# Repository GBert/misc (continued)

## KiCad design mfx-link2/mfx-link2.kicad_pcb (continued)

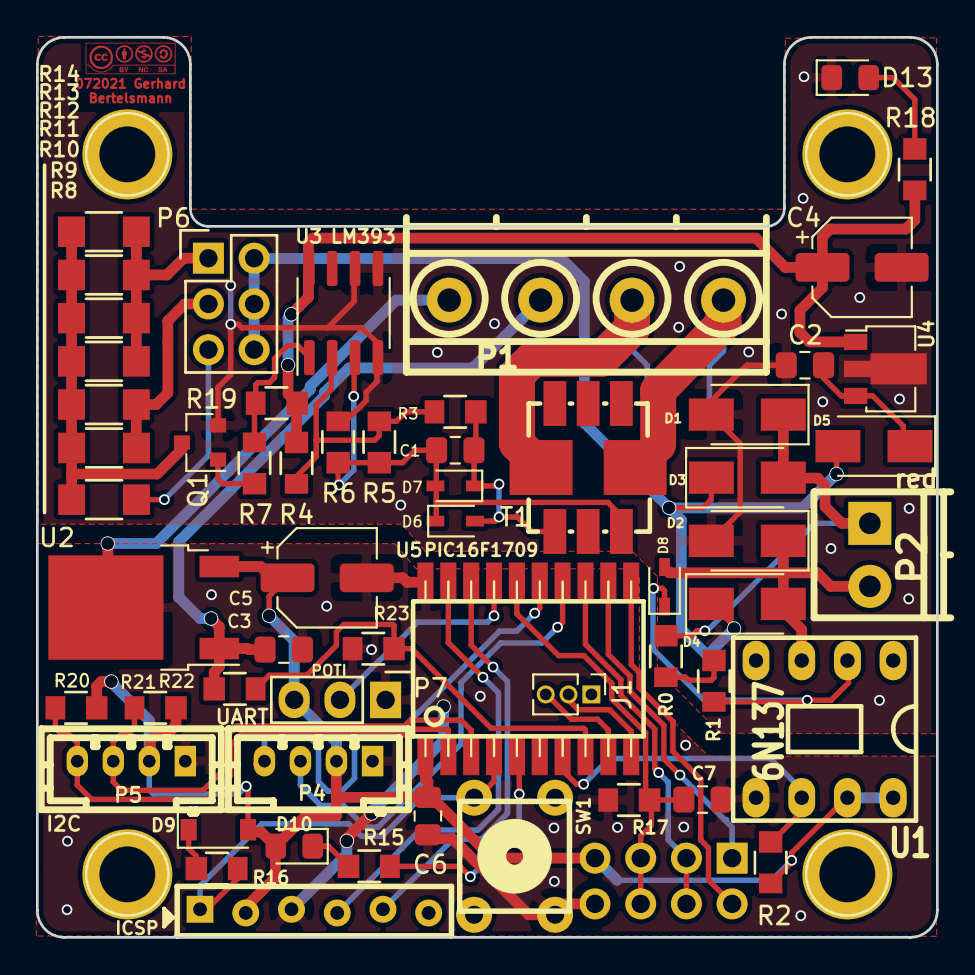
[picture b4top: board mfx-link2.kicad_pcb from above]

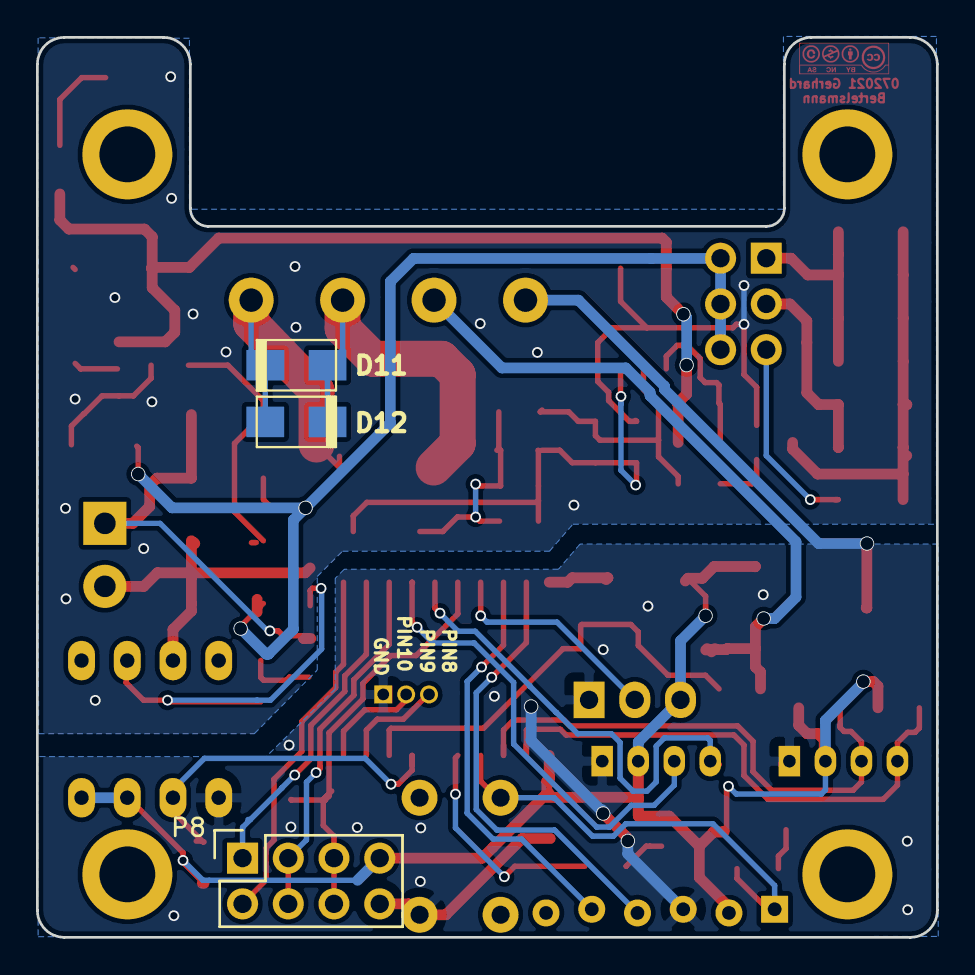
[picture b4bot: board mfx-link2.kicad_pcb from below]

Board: 2 copper layers, 50.0 x 50.0 mm, 61 parts (3 on the bottom side), 42 nets.

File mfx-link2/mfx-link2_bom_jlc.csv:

"Comment","Designator","Footprint","LCSC Part #"
"100nF","C6,C1,C3,C2","C_0805_2012Metric_Pad1.18x1.45mm_HandSolder","C49678"
"1nF","C7","C_0805_2012Metric_Pad1.18x1.45mm_HandSolder","C46653"
"US1M","D4,D3,D2,D5,D12,D11,D1","D_SMA","C412437"
"1N4148","D6,D7,D8","D_SOD-323F","C2128"
"B5819W","D9","D_SOD-123","C8598"
"LEDR","D10","LED_0805","C84256"
"LED","D13","LED_0805","C34499"
"MMBT5551","Q1","SOT-23","C2145"
"820","R1,R0","R_0805_HandSolderingII","C17837"
"390","R2","R_0805_HandSolderingII","C17655"
"22","R3","R_0805_HandSolderingII","C17561"
"82","R5","R_0805_HandSolderingII","C17841"
"1k","R7","R_0805_HandSolderingII","C17513"
"1K","R9,R8","R_1206_HandSolderingII","C4410"
"1k","R11,R12,R13,R14,R10","R_1206_HandSolderingII","C4410"
"1k5","R15","R_0805_HandSolderingII","C4310"
"4k7","R16,R6,R4,R19","R_0805_HandSolderingII","C17673"
"10k","R17,R23","R_0805_HandSolderingII","C17414"
"560","R18","R_0805_HandSolderingII","C28636"
"3k3","R20,R21","R_0805_HandSolderingII","C26010"
"39k","R22","R_0805_HandSolderingII","C25826"
"7805","U2","TO-252-2","C58069"
"LM393","U3","SOIC-8_3.9x4.9mm_P1.27mm","C7955"
"78L05","U4","SOT-89-3","C71136"

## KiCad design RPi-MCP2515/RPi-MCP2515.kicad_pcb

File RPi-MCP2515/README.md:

RPI-I2C/CAN Adapter mit galv. Trennung
======================================

Hinweis
-------
In der Platinen-Version 1.0 hatte sich ein Fehler eingeschlichen so das der Längsregler MC7805 spiegelverkehrt eingebaut werden musste. Das ist mit der Version >= 1.1 behoben, d.h. das der Längsregler wie auf dem Bestückungsdruck ersichtlich eingebaut werden muss.

[Reichelt Liste (ohne P82B715P)](https://www.reichelt.de/my/1344615) Variante mit galvanischer Trennung und externer Spannungsversorgung

Bauteilliste
------------
(galv. Trennung mit ISO1050)
```
C1,C2	22pF
C3-C9	100nF
D1	LED 2mA
P1	Buchsenleiste 2x20
P6	Steckerleiste 1x2
P9	Groove Buchse gewinkelt
P17	Steckerleiste 1x2
R1-R3	4k7 Ohm
R5	1k5 Ohm
R13	120 Ohm
R14,R15	3k3 Ohm
R24,R25	3k3 Ohm
U1	MCP2515
U3	(P82B715 optional)
U6	ISO1050
U7	LM7805
Y1	16MHz Quarz
```

Aufbau
------
Die CAN-Anbindung erfolgt bei der Nutzung des ISO1050 über P7 mit VCOM (7-24V), GND, CANL und CANH.

Wird ein galv. getrennter DCDC Konverter verwendet so sind nur GND, CANL und CANH zu verbinden. 

Sollte ein MCP2562 eingesetzt werden erfolgt die Anbindung über P3.

Nutzung MS2 Kabel E146781
-------------------------

|Farbe	  |Funktion|
|---------|--------|
|schwarz  |	GND|	
|braun	  |    CANL|	
|orange   |    CANH|	
|rot      | 18V Vcc|

Nutzung
-------

Mit dem I2C Interface kann man die preiswerten [PI02](http://wiki.rocrail.net/doku.php?id=gca_pi02-de) nutzen.
pio-i2c-udp setzt Events in das M\*rklin Format um und stellt sich als S88 dar.

CAN Nutzung vorbereiten
```
sudo apt-get update
sudo apt-get upgrade
sudo apt-get install can-utils
```
/boot/config.txt editieren
```
; uncomment
dtparam=spi=on
; add
dtoverlay=mcp2515-can0,oscillator=16000000,interrupt=25
```
reboot
```
sudo shutdown -r now
```
CAN Interface konfigurieren
```
sudo ip link set can0 up type can bitrate 250000 restart-ms 100
```
bzw: die Datei /etc/network/interfaces.d/can0 wie folgt anlegen:
```
auto can0
iface can0 inet manual
        pre-up /sbin/ip link set $IFACE type can bitrate 250000 restart-ms 100
        up /sbin/ifconfig $IFACE up
        down /sbin/ifconfig $IFACE down
```
can2lan nutzen
```
sudo apt-get install lighttpd
# zumindest geraet.vrs unter /var/www/html/config/ anlegen:
sudo mkdir -p /var/www/html/config/
sudo cat << EOF > /var/www/html/config/geraet.vrs
[geraet]
version
 .minor=1
geraet
 .sernum=1
 .hardvers=RPi,3
EOF

```
can2lan herunter laden und starten
```
cd
sudo apt-get install git libpcap-dev
git clone https://github.com/GBert/railroad.git
cd railroad/can2udp/src
make
sudo cp can2lan /usr/sbin/
sudo cp can-monitor /usr/bin/
sudo cp ../files/maerklin/config/gleisbild.cs2 /var/www/html/gleisbild.cs2

# Debian  Init Skript installieren und testen
sudo cp ../debian/can2lan.init /etc/init.d
sudo /etc/init.d/can2lan.init start
sudo /etc/init.d/can2lan.init status
sudo /etc/init.d/can2lan.init stop

sudo update-rc.d can2lan.init defaults

# oder manuell im Vordergrund start
can2lan -mvf -c /var/www/html
```

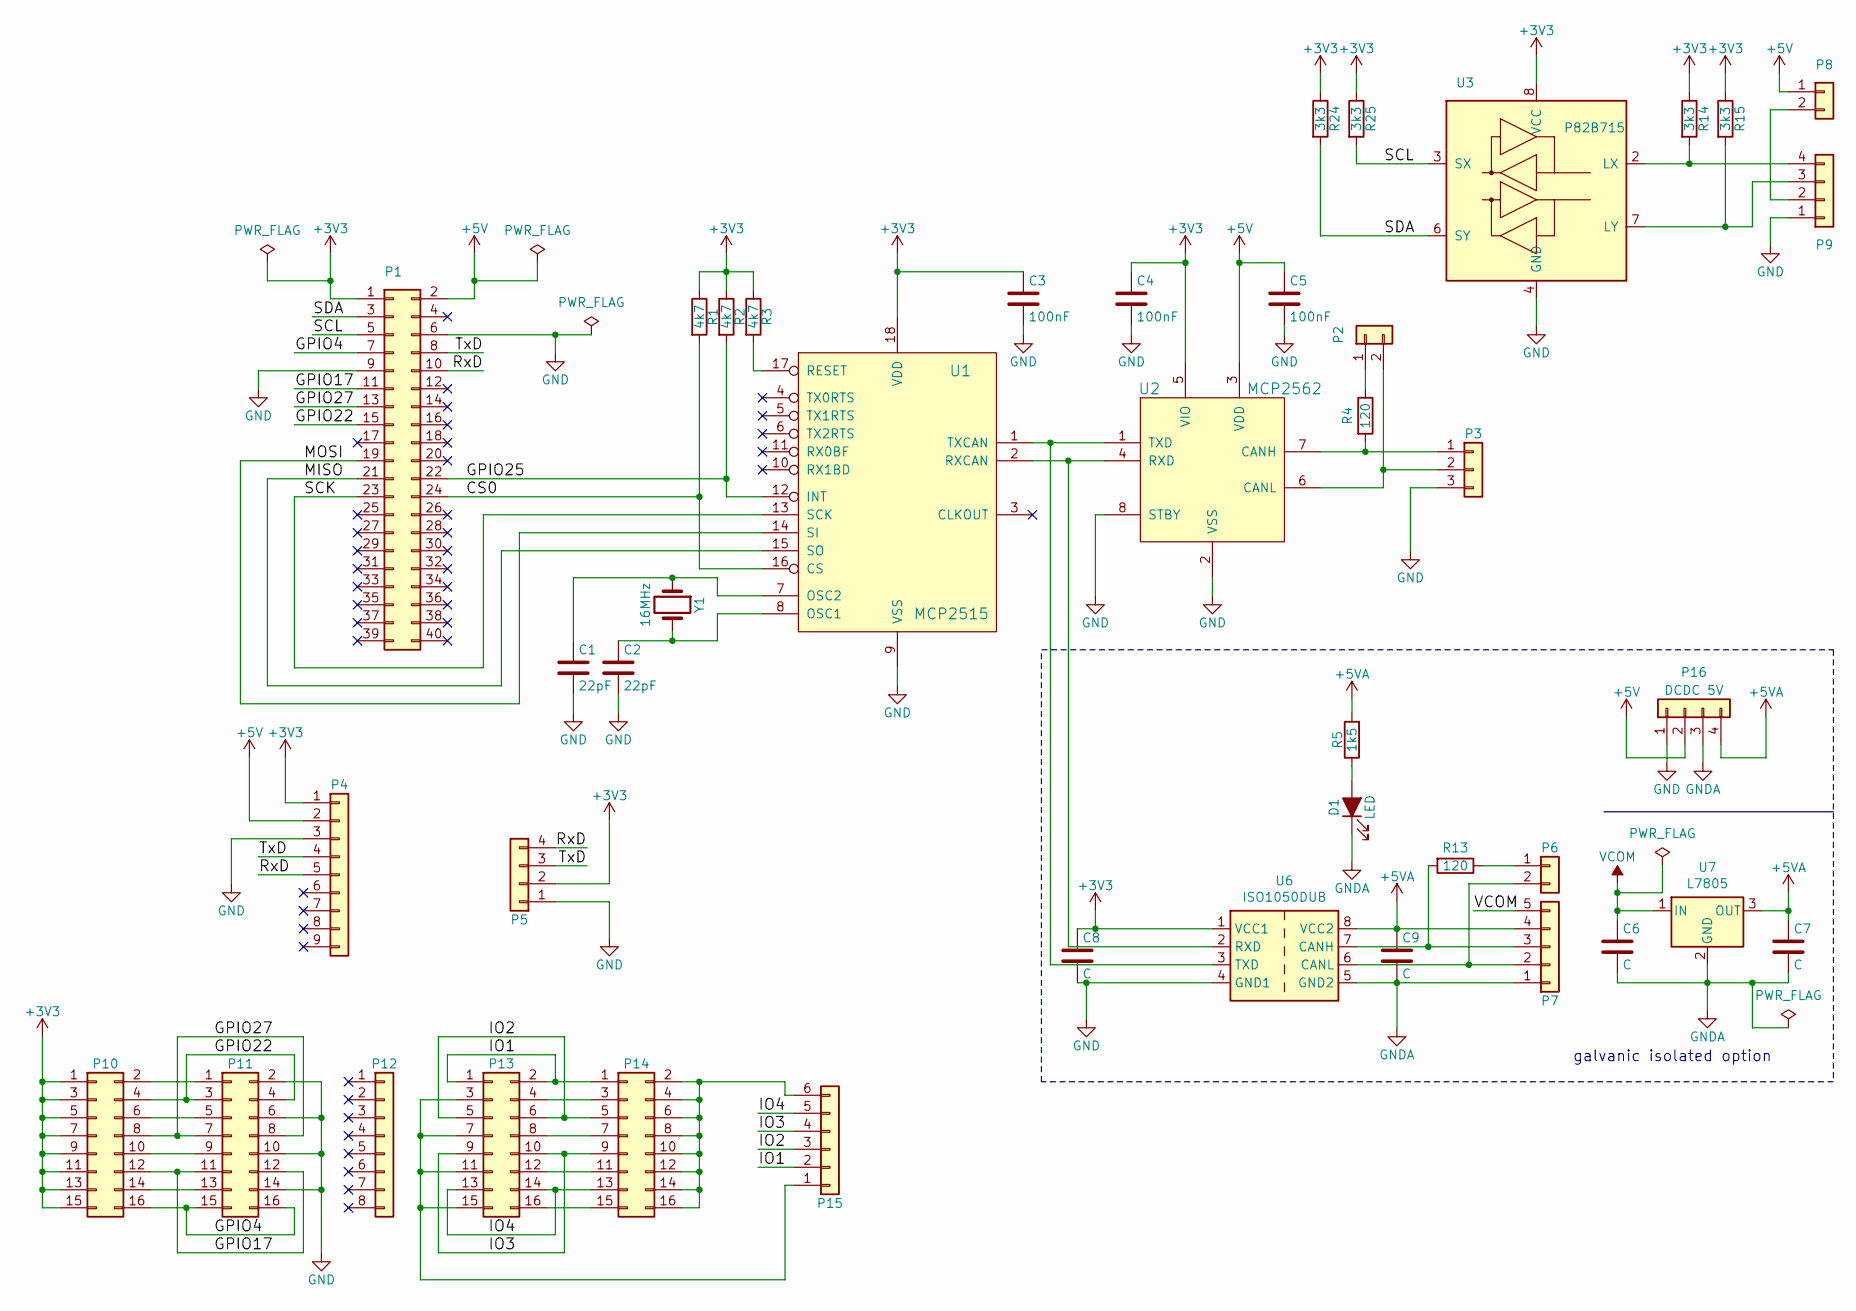
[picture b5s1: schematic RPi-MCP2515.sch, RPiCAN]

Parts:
C1, C2: 22pF; C_Disc_D3_P2.5
C3, C4, C5: 100nF; C_Disc_D3_P2.5
C6, C7, C8, C9: C; C_Disc_D3_P2.5
D1: LED; LED-5MM
P1: CONN_02X20; Socket_Strip_Straight_2x20
P2, P6, P8: CONN_01X02; Pin_Header_Straight_1x02
P3: CONN_01X03; Pin_Header_Angled_1x03
P4: CONN_01X09; Pin_Header_Straight_1x09
P5, P9: CONN_01X04; s4b-ph-kl
P7: CONN_01X05; pt_1,5-5-3,5-h
P10, P11, P13, P14: CONN_02X08; Socket_Strip_Straight_2x08
P12: CONN_01X08; Socket_Strip_Straight_1x08
P15: CONN_01X06; Socket_Strip_Straight_1x06
P16: DCDC 5V; dcdc_sil4
R1, R2, R3: 4k7; RC03
R4, R13: 120; RC03
R5: 1k5; RC03
R14, R15, R24, R25: 3k3; RC03
U1: MCP2515; dil_18-300_socket
U2: MCP2562; dil_8-300_socket
U3: P82B715; dil_8-300_socket
U6: ISO1050DUB; mdip_8
U7: L7805; TO-220_Neutral123_Horizontal
Y1: 16MHz; crystal_hc-49s

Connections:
+3V3: C3.1, C4.1, C8.1, P1.1, P4.1, P5.2, P10.1, P10.3, P10.5, P10.7, P10.9, P10.11, P10.13, P10.15, R1.1, R2.1, R3.1, R14.1, R15.1, R24.1, R25.1, U1.18 (VDD~), U2.5 (VIO~), U3.8 (VCC), U6.1 (VCC1)
+5V: C5.1, P1.2, P4.2, P8.1, P16.2, U2.3 (VDD~)
+5VA: C7.1, C9.1, P7.4, P16.4, R5.2, U6.8 (VCC2), U7.3 (OUT)
/CS0: P1.24, R1.2, U1.16 (CS~)
/GPIO4: P1.7, P10.16, P11.15, P11.16
/GPIO17: P1.11, P10.12, P11.11, P11.12
/GPIO22: P1.15, P10.4, P11.3, P11.4
/GPIO25: P1.22, R2.2, U1.12 (INT~)
/GPIO27: P1.13, P10.8, P11.7, P11.8
/IO1: P13.1, P13.2, P14.1, P15.2
/IO2: P13.5, P13.6, P14.5, P15.3
/IO3: P13.9, P13.10, P14.9, P15.4
/IO4: P13.13, P13.14, P14.13, P15.5
/MISO: P1.21, U1.15 (SO~)
/MOSI: P1.19, U1.14 (SI~)
/RxD: P1.10, P4.5, P5.4
/SCK: P1.23, U1.13 (SCK~)
/SCL: P1.5, R25.2, U3.3 (SX)
/SDA: P1.3, R24.2, U3.6 (SY)
/TxD: P1.8, P4.4, P5.3
GND: C1.2, C2.2, C3.2, C4.2, C5.2, C8.2, P1.6, P1.9, P3.3, P4.3, P5.1, P9.1, P11.2, P11.6, P11.10, P11.14, P16.1, U1.9 (VSS~), U2.2 (VSS~), U2.8 (STBY), U3.4 (GND), U6.4 (GND1)
GNDA: C6.2, C7.2, C9.2, D1.1 (K), P7.1, P16.3, U6.5 (GND2), U7.2 (GND)
unnamed: C1.1, U1.7 (OSC2~), Y1.1
unnamed: C2.1, U1.8 (OSC1~), Y1.2
unnamed: D1.2 (A), R5.1
unnamed: P2.1, R4.1
unnamed: P2.2, P3.2, U2.6 (CANL)
unnamed: P3.1, R4.2, U2.7 (CANH)
unnamed: P6.1, R13.1
unnamed: P6.2, P7.2, U6.6 (CANL)
unnamed: P7.3, R13.2, U6.7 (CANH)
unnamed: P8.2, P9.2
unnamed: P9.3, R15.2, U3.7 (LY)
unnamed: P9.4, R14.2, U3.2 (LX)
unnamed: P10.2, P11.1
unnamed: P10.6, P11.5
unnamed: P10.10, P11.9
unnamed: P10.14, P11.13
unnamed: P13.4, P14.3
unnamed: P13.8, P14.7
unnamed: P13.3, P13.7, P13.11, P13.15, P15.1
unnamed: P13.12, P14.11
unnamed: P13.16, P14.15
unnamed: P14.2, P14.4, P14.6, P14.8, P14.10, P14.12, P14.14, P14.16, P15.6
unnamed: R3.2, U1.17 (RESET~)
unnamed: U1.1 (TXCAN~), U2.1 (TXD), U6.3 (TXD)
unnamed: U1.2 (RXCAN~), U2.4 (RXD), U6.2 (RXD)
VCOM: C6.1, P7.5, U7.1 (IN)

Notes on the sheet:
galvanic isolated option

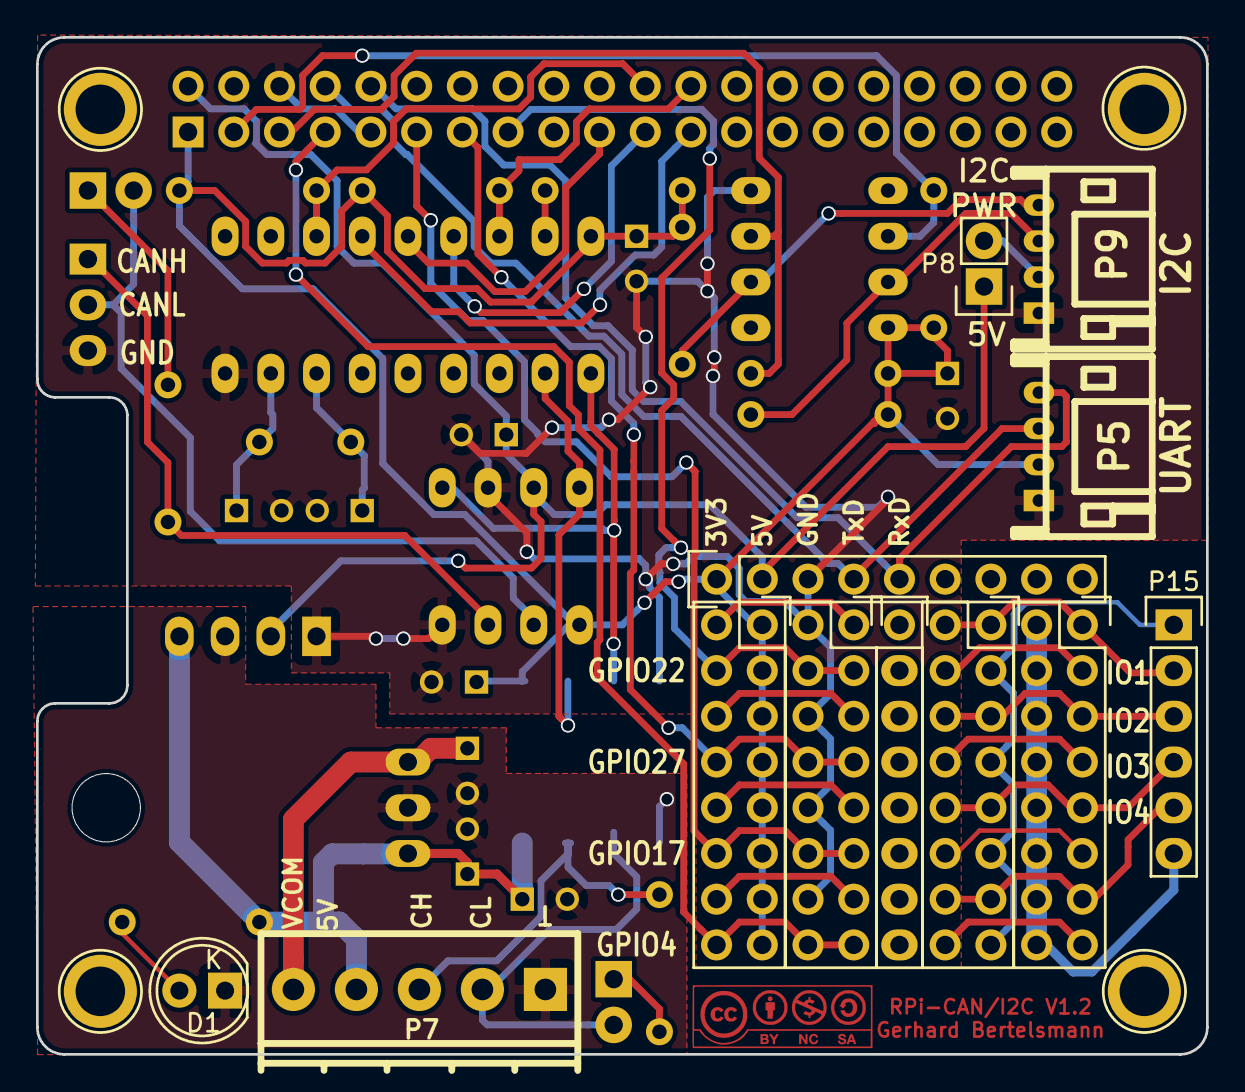
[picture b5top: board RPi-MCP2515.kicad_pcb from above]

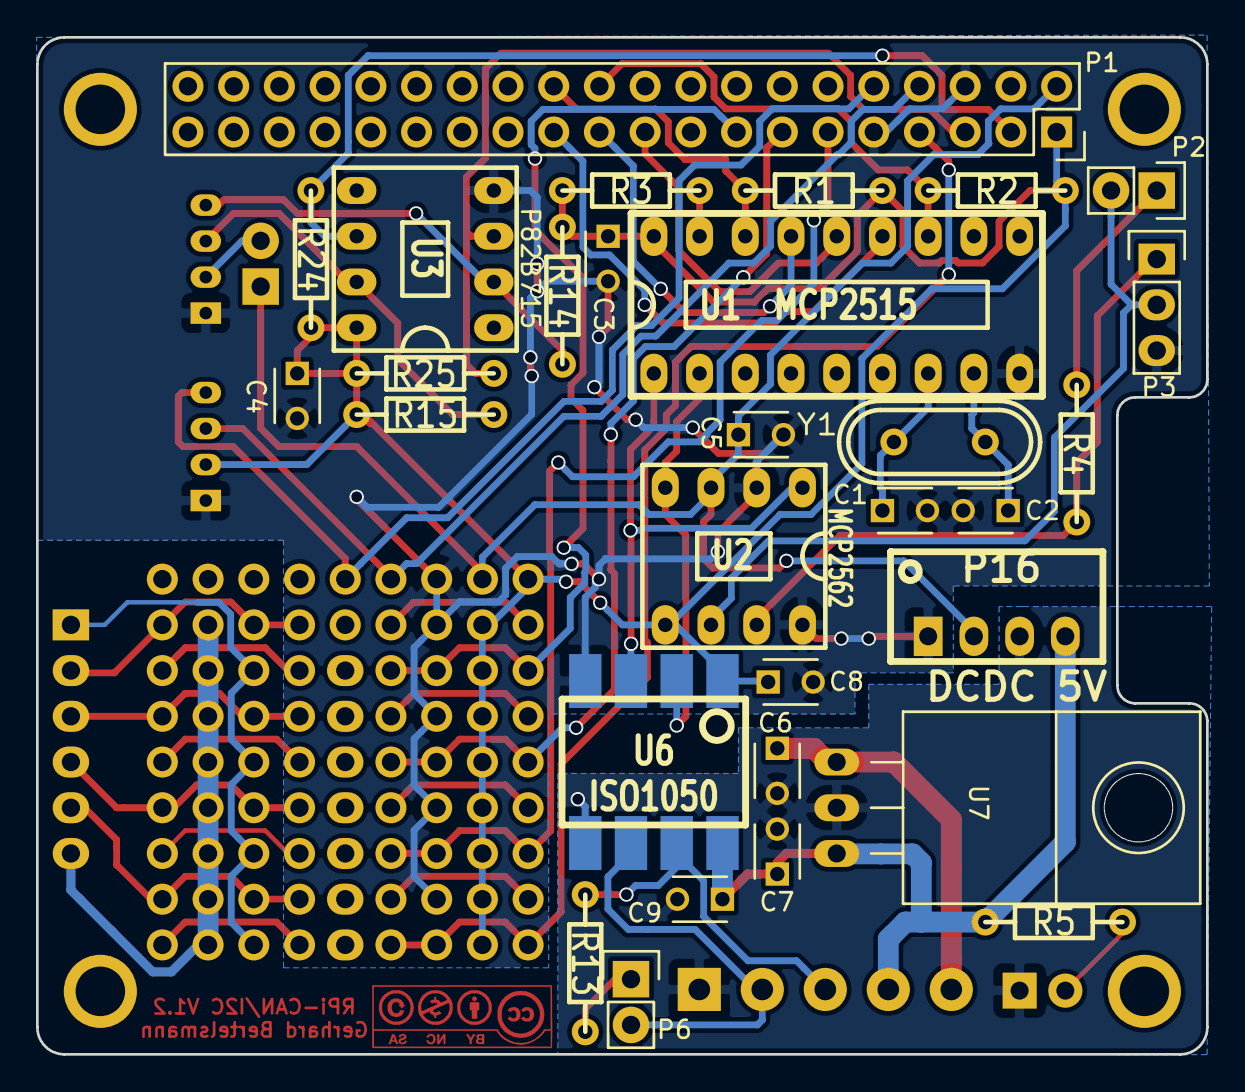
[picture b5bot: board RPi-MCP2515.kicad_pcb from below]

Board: 2 copper layers, 65.0 x 56.5 mm, 42 parts (30 on the bottom side), 48 nets.

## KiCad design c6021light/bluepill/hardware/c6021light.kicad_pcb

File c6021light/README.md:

connect6021 light für Keyboard 6040
===================================

Belegung der Buchse (Keyboard 6040 links)
```
SDA  SCL                      8V   8V
 2b   4b   6b   8b  10b  12b  14b  16b
 2a   4a   6a   8a  10a  12a  14a  16a
GND  GND  GND  GND  GND  GND  GND  GND
```

Federleiste DIN 41612 32-pol B/2
z.B. ept 102-90065

http://dl1zax.selfhost.de/ATMega/PDF/6022.pdf

```
Für die Übertragung von Weichenstellbefehlen genügen drei Byte als Schaltanforderung.
Es sind dies die Bytes für Empfänger (Zentrale), Keyboard-Nr. (0 bis 15) und das Datenbyte.
Das Datenbyte enthält die Angabe der Decoder-Ausgangsnummer (Bits 0 bis 3) und der Decoder- Teiladresse (Bits 4 und 5).
Mit Bit 0 wird die Schaltrichtung bestimmt (0=Rot, 1=Grün), mit Bit 3 wird der Schaltstrom eingeschaltet.
Da mit einem Keyboard (6040) vier Decoder angesprochen werden können, bestimmen die Bits 4 und 5, um welche Vierergruppe von Tastenpaaren und somit für welchen der vier für dieses Keyboard zuständigen Decoder sich der Schaltbefehl handelt.
Bei der Bildung der realen Decoder-Adresse (im binären Zahlenformat) stellen diese zwei Bits die Bits 0 und 1 dar. Die vier Bits der Keyboard-Adresse bilden dann die Bits 2 bis 5 der Decoder-Adresse. Diese Decoder-Adresse wird noch um 1 erhöht, da die Decoder-Adressierung im Märklin Digital-System immer mit der Adresse "01" beginnt. Somit können maximal 64 Decoder im Bereich von "01" bis "64" angesprochen werden.
Aufbau des Datenbytes:

    Bit 0 = Schaltrichtung, 0=Rot, 1=Grün
    Bit 1 = Decoderausgang LSB (Least Significant Bit)
    Bit 2 = Decoderausgang MSB (Most Significant Bit)
    Bit 3 = Schaltstrom, 0=aus, 1=ein
    Bit 4 = Decoder-Teiladresse LSB
    Bit 5 = Decoder-Teiladresse MSB 

Aufbau der Schaltanforderung:

Empfänger		Sender			Datenbyte		Stoppbits
1111 1110	0	001X XXX0	0	00XX XXXX	0	10
Zentrale	Q	Geräte-Adr.	Q			Q

Die Bestätigung von der Zentrale lautet:

Empfänger		Sender			Datenbyte		Stoppbit
001X XXX0	0	1111 1110	0	00XX XXXX	0	0
Geräte-Adr.	Q	Zentrale	Q			Q

```

Sequenz

Taste 0 rot

0xfe 0x20 0x08

0x20 0xfe 0x08 (Osci wA 0x10 -> Data 0x20)

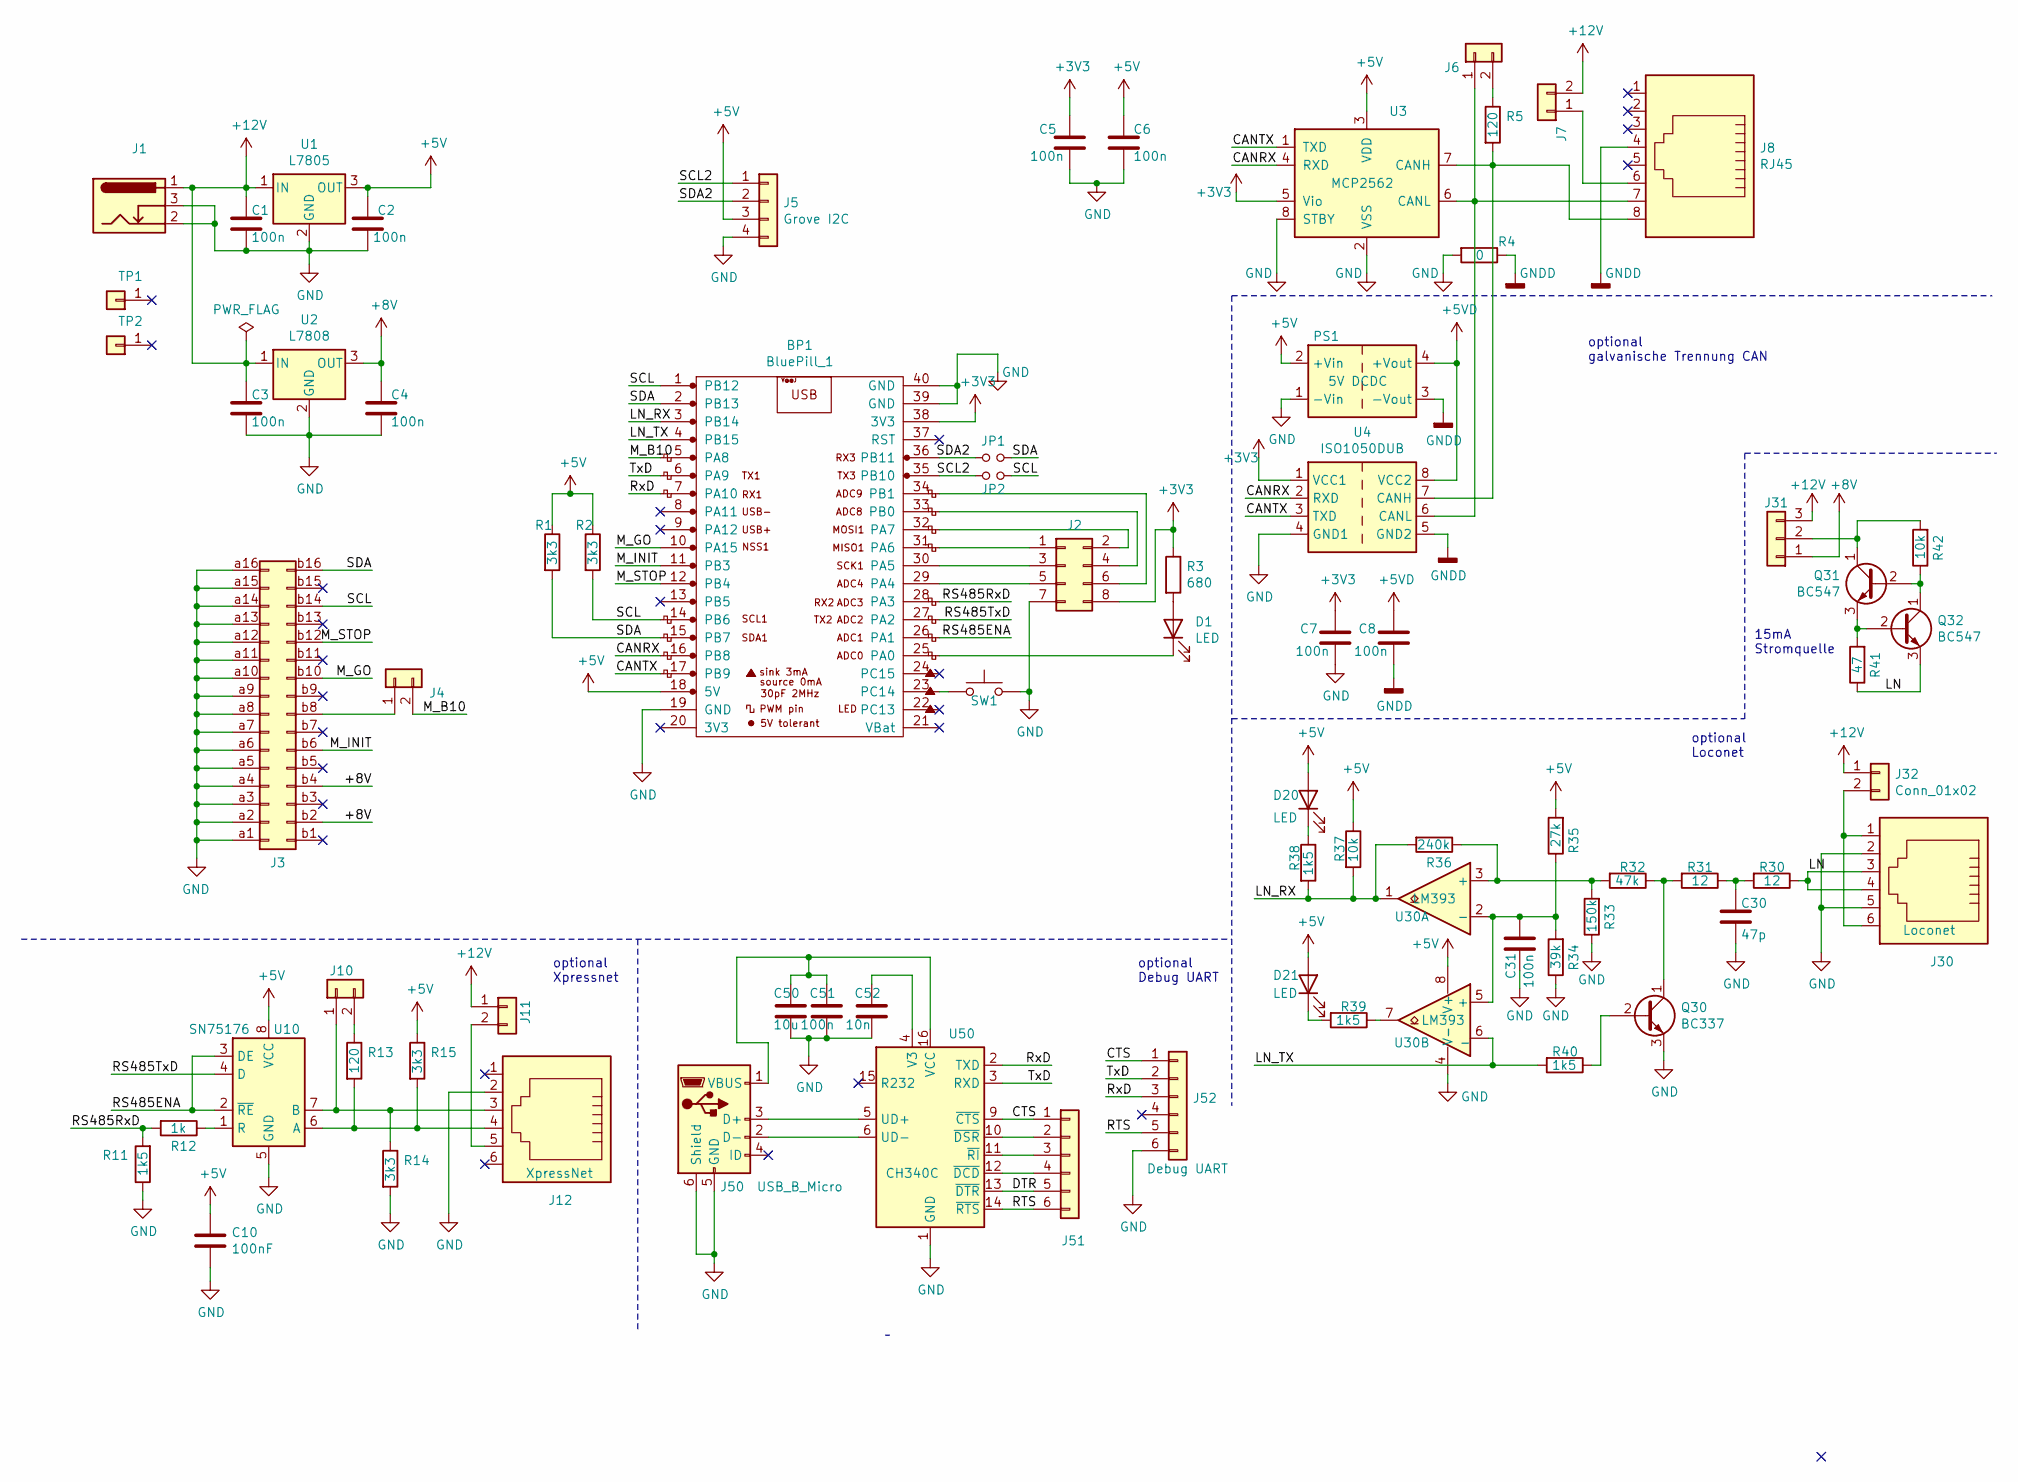
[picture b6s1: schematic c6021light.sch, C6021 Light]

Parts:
BP1: BluePill_1; YAAJ_BluePill
C1, C2, C3, C4, C5, C6, C7, C8, C31: 100n; C_Disc_D3.0mm_W1.6mm_P2.50mm
C10: 100nF; C_Disc_D3.0mm_W1.6mm_P2.50mm
C30: 47p; C_Rect_L7.0mm_W3.5mm_P2.50mm_P5.00mm
C50: 10u; C_0805_2012Metric
C51: 100n; C_0805_2012Metric
C52: 10n; C_0805_2012Metric
D1, D20, D21: LED; LED_D3.0mm
J1: Barrel_Jack_Switch; dc_socket
J2: Conn_02x04_Odd_Even; PinHeader_2x04_P2.54mm_Vertical
J3: Conn_02x16_Row_Letter_First; DIN41612_B2_2x16_Female_Vertical_THT
J4, J6, J7, J10, J11, J32: Conn_01x02; PinHeader_1x02_P2.54mm_Vertical_NB
J5: Grove I2C; b4b-ph-kl
J8: RJ45; mebp8
J12: XpressNet; RJ12_Amphenol_54601
J30: Loconet; RJ12_Amphenol_54601
J31: Conn_01x03; PinHeader_1x03_P2.54mm_Vertical
J50: USB_B_Micro; USB_Micro-B_Molex-105017-0001
J51: Conn_01x06; PinHeader_1x06_P1.27mm_Vertical
J52: Debug UART; PinHeader_1x06_P2.54mm_Vertical
JP1, JP2: Jumper_NO_Small; PinHeader_1x02_P2.54mm_Vertical
PS1: 5V DCDC; Converter_DCDC_Murata_MEE1SxxxxSC_THT
Q30: BC337; TO-92_Inline
Q31, Q32: BC547; TO-92_Inline
R1, R2: 3k3; R_Axial_DIN0207_L6.3mm_D2.5mm_P7.62mm_Horizontal
R3: 680; R_Axial_DIN0207_L6.3mm_D2.5mm_P7.62mm_Horizontal
R4: 0; R_AXIAL_0_WIRE
R5: 120; R_Axial_DIN0207_L6.3mm_D2.5mm_P7.62mm_Horizontal
R11, R38, R39, R40: 1k5; R_Axial_DIN0207_L6.3mm_D2.5mm_P7.62mm_Horizontal
R12: 1k; R_Axial_DIN0207_L6.3mm_D2.5mm_P7.62mm_Horizontal
R13: 120; RC03
R14, R15: 3k3; RC03
R30, R31: 12; R_Axial_DIN0207_L6.3mm_D2.5mm_P7.62mm_Horizontal
R32: 47k; R_Axial_DIN0207_L6.3mm_D2.5mm_P7.62mm_Horizontal
R33: 150k; R_Axial_DIN0207_L6.3mm_D2.5mm_P7.62mm_Horizontal
R34: 39k; R_Axial_DIN0207_L6.3mm_D2.5mm_P7.62mm_Horizontal
R35: 27k; R_Axial_DIN0207_L6.3mm_D2.5mm_P7.62mm_Horizontal
R36: 240k; R_Axial_DIN0207_L6.3mm_D2.5mm_P7.62mm_Horizontal
R37: 10k; R_Axial_DIN0207_L6.3mm_D2.5mm_P7.62mm_Horizontal
R41: 47; RC03
R42: 10k; RC03
SW1: SW_Push; PCB_PUSH
TP1, TP2: Conn_01x01; Test_Point_NA
U1: L7805; TO-220-3_Vertical
U2: L7808; TO-220-3_Vertical
U3: MCP2562; dil_8-300_socket
U4: ISO1050DUB; SOP-8_6.62x9.15mm_P2.54mm
U10: SN75176; dil_8-300_socket
U30: LM393; dil_8-300_socket
U50: CH340C; SOIC-16_3.9x9.9mm_P1.27mm

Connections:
+3V3: BP1.38 (3V3), C5.1, C7.1, J2.8, R3.1, U3.5 (Vio), U4.1 (VCC1)
+5V: BP1.18 (5V), C2.1, C6.1, C10.1, D20.2 (A), D21.2 (A), J5.3, PS1.2 (+Vin), R1.1, R2.1, R15.1, R35.2, R37.1, U1.3 (OUT), U3.3 (VDD), U10.8 (VCC), U30.8 (V+)
+5VD: C8.1, PS1.4 (+Vout), U4.8 (VCC2)
+8V: C4.1, J3.b2, J3.b4, J31.1, U2.3 (OUT)
+12V: C1.1, C3.1, J1.1, J7.2, J11.1, J31.3, J32.1, U1.1 (IN), U2.1 (IN)
/CANRX: BP1.16 (PB8), U3.4 (RXD), U4.2 (RXD)
/CANTX: BP1.17 (PB9), U3.1 (TXD), U4.3 (TXD)
/CTS: J51.1, J52.1, U50.9 (~CTS)
/DTR: J51.5, U50.13 (~DTR)
/LN: J30.3, J30.4, Q32.3 (E), R30.1, R41.1
/LN_RX: BP1.3 (PB14), R36.2, R37.2, R38.2, U30.1
/LN_TX: BP1.4 (PB15), R40.2, U30.6 (_)
/M_B10: BP1.5 (PA8), J4.2
/M_GO: BP1.10 (PA15), J3.b10
/M_INIT: BP1.11 (PB3), J3.b6
/M_STOP: BP1.12 (PB4), J3.b12
/RS485ENA: BP1.26 (PA1), U10.2 (~RE), U10.3 (DE)
/RS485RxD: BP1.28 (PA3), R11.2, R12.2
/RS485TxD: BP1.27 (PA2), U10.4 (D)
/RTS: J51.6, J52.5, U50.14 (~RTS)
/RxD: BP1.7 (PA10), J52.3, U50.2 (TXD)
/SCL: BP1.1 (PB12), BP1.14 (PB6), J3.b14, JP2.2, R2.2
/SCL2: BP1.35 (PB10), J5.1, JP2.1
/SDA: BP1.2 (PB13), BP1.15 (PB7), J3.b16, JP1.2, R1.2
/SDA2: BP1.36 (PB11), J5.2, JP1.1
/TxD: BP1.6 (PA9), J52.2, U50.3 (RXD)
GND: BP1.19 (GND), BP1.39 (GND), BP1.40 (GND), C1.2, C2.2, C3.2, C4.2, C5.2, C6.2, C7.2, C10.2, C30.2, C31.2, C50.2, C51.2, C52.2, J1.2, J1.3, J2.7, J3.a1, J3.a2, J3.a3, J3.a4, J3.a5, J3.a6, J3.a7, J3.a8, J3.a9, J3.a10, J3.a11, J3.a12, J3.a13, J3.a14, J3.a15, J3.a16, J5.4, J12.2, J30.2, J30.5, J50.5 (GND), J50.6 (Shield), J52.6, PS1.1 (-Vin), Q30.3 (E), R4.2, R11.1, R14.2, R33.1, R34.1, SW1.2, U1.2 (GND), U2.2 (GND), U3.2 (VSS), U3.8 (STBY), U4.4 (GND1), U10.5 (GND), U30.4 (V-), U50.1 (GND)
GNDD: C8.2, J8.4, PS1.3 (-Vout), R4.1, U4.5 (GND2)
unnamed: BP1.23 (PC14), SW1.1
unnamed: BP1.25 (PA0), D1.1 (K)
unnamed: BP1.29 (PA4), J2.5
unnamed: BP1.30 (PA5), J2.3
unnamed: BP1.31 (PA6), J2.1
unnamed: BP1.32 (PA7), J2.2
unnamed: BP1.33 (PB0), J2.4
unnamed: BP1.34 (PB1), J2.6
unnamed: C30.1, R30.2, R31.1
unnamed: C31.1, R34.2, R35.1, U30.2 (-), U30.5 (+)
unnamed: C50.1, C51.1, J50.1 (VBUS), U50.16 (VCC)
unnamed: C52.1, U50.4 (V3)
unnamed: D1.2 (A), R3.2
unnamed: D20.1 (K), R38.1
unnamed: D21.1 (K), R39.2
unnamed: J3.b8, J4.1
unnamed: J6.1, J8.7, U3.6 (CANL), U4.6 (CANL)
unnamed: J6.2, R5.1
unnamed: J7.1, J8.6
unnamed: J8.8, R5.2, U3.7 (CANH), U4.7 (CANH)
unnamed: J10.1, J12.3, R14.1, U10.7 (B)
unnamed: J10.2, R13.1
unnamed: J11.2, J12.5
unnamed: J12.4, R13.2, R15.2, U10.6 (A)
unnamed: J30.1, J30.6, J32.2
unnamed: J31.2, Q31.1 (C), R42.2
unnamed: J50.2 (D-), U50.6 (UD-)
unnamed: J50.3 (D+), U50.5 (UD+)
unnamed: J51.2, U50.10 (~DSR)
unnamed: J51.3, U50.11 (~RI)
unnamed: J51.4, U50.12 (~DCD)
unnamed: Q30.1 (C), R31.2, R32.1
unnamed: Q30.2 (B), R40.1
unnamed: Q31.2 (B), Q32.1 (C), R42.1
unnamed: Q31.3 (E), Q32.2 (B), R41.2
unnamed: R12.1, U10.1 (R)
unnamed: R32.2, R33.2, R36.1, U30.3 (+)
unnamed: R39.1, U30.7

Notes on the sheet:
optional Xpressnet
optional Debug UART
optional Loconet
optional galvanische Trennung CAN
15mA Stromquelle

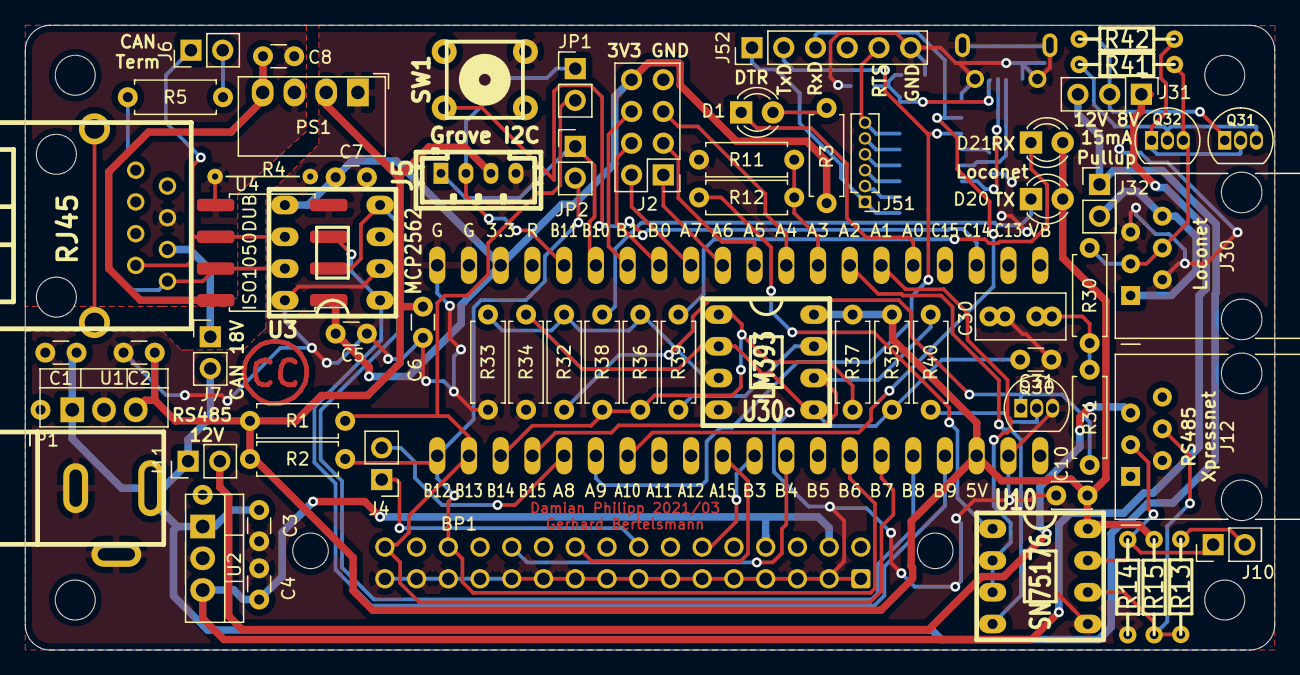
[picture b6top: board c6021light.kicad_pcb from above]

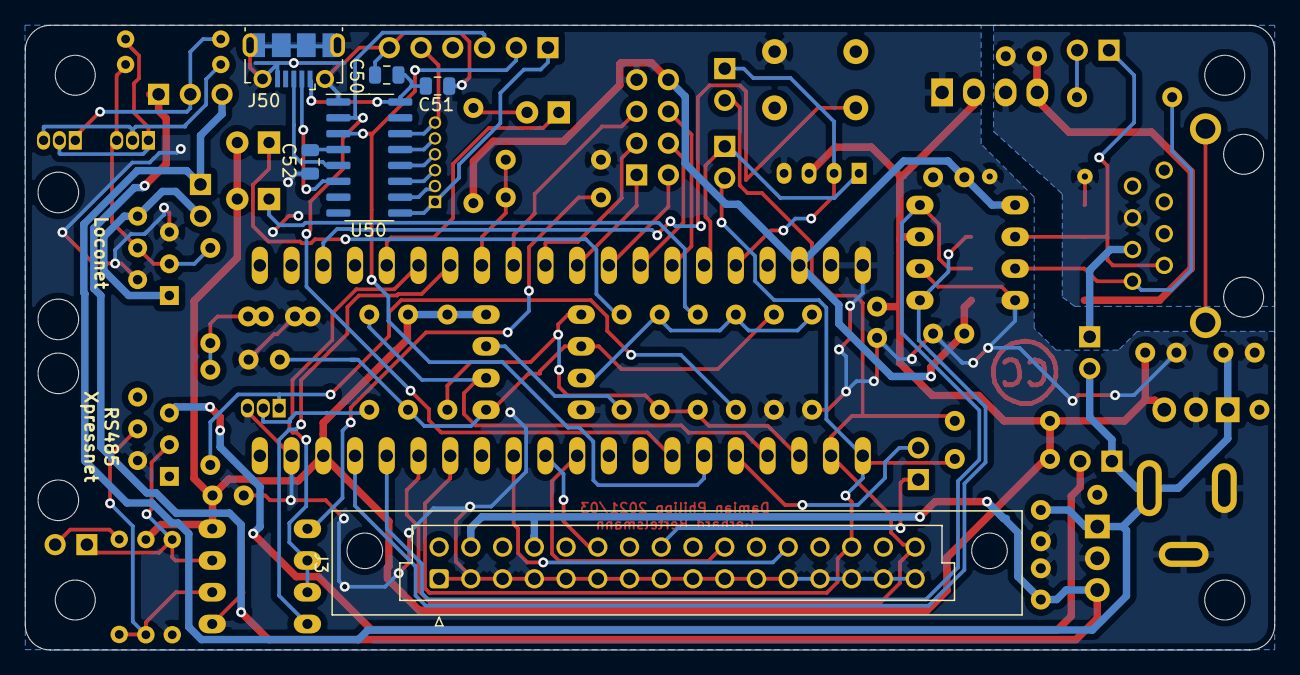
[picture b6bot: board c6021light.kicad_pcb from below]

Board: 2 copper layers, 100.0 x 50.0 mm, 74 parts (6 on the bottom side), 66 nets.

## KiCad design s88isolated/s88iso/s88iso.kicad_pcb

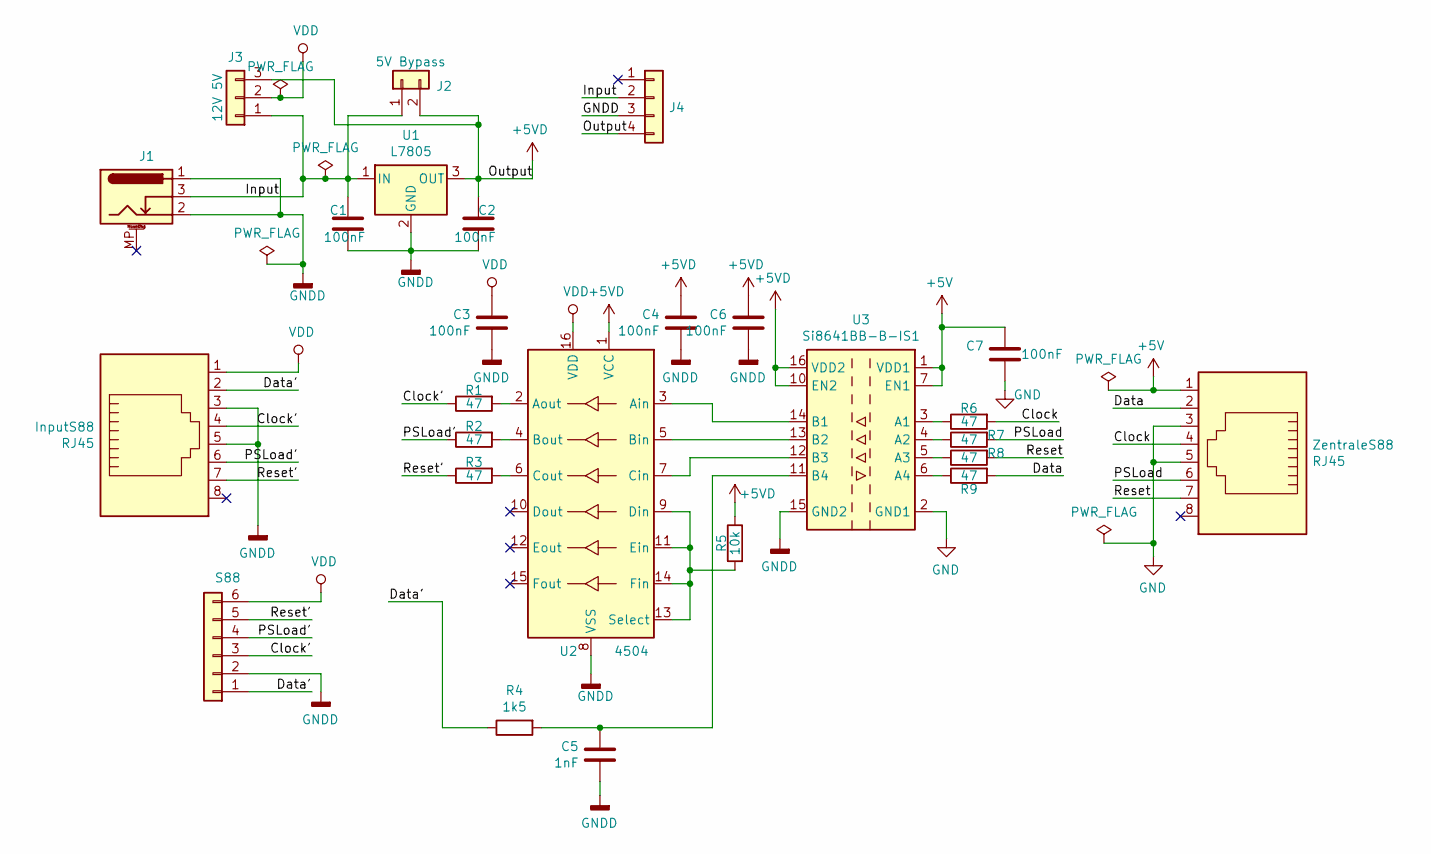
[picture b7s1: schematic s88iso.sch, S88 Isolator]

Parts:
C1, C2, C3, C4, C6, C7: 100nF; C_0805_2012Metric
C5: 1nF; C_0805_2012Metric
InputS88: RJ45; megb8-8-Uni
J1: Barrel_Jack_Switch_MountingPin; dc_socket
J2: 5V Bypass; PinHeader_1x02_P2.54mm_Vertical
J3: 12V 5V; PinHeader_1x03_P2.54mm_Vertical
J4: Conn_01x04; PinSocket_1x04_P2.54mm_Vertical
R1, R2, R3, R6, R7, R8, R9: 47; R_0805_2012Metric
R4: 1k5; R_0805_2012Metric
R5: 10k; R_0805_2012Metric
S88: Conn_01x06; PinSocket_1x06_P2.54mm_Horizontal
U1: L7805; TO-252-2
U2: 4504; so-16
U3: Si8641BB-B-IS1; so-16
ZentraleS88: RJ45; megb8-8-Uni

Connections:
+5V: C7.1, U3.1 (VDD1), U3.7 (EN1), ZentraleS88.1; also elsewhere on the board
+5VD: C2.1, C4.1, C6.1, J2.2, J3.3, J4.4, R5.1, U1.3 (OUT), U2.1 (VCC), U3.10 (EN2), U3.16 (VDD2)
/Clock: R6.2, ZentraleS88.4; also elsewhere on the board
/Clock': InputS88.4, R1.1, S88.3; also elsewhere on the board
/Data: R9.2, ZentraleS88.2; also elsewhere on the board
/Data': InputS88.2, R4.1, S88.1; also elsewhere on the board
/Input: C1.1, J1.3, J2.1, J3.1, J4.2, U1.1 (IN)
/PSLoad: R7.2, ZentraleS88.6; also elsewhere on the board
/PSLoad': InputS88.6, R2.1, S88.4; also elsewhere on the board
/Reset: R8.2, ZentraleS88.7; also elsewhere on the board
/Reset': InputS88.7, R3.1, S88.5; also elsewhere on the board
GND: C7.2, U3.2 (GND1), U3.8 (GND1), ZentraleS88.3, ZentraleS88.5; also elsewhere on the board
GNDD: C1.2, C2.2, C3.2, C4.2, C5.2, C6.2, InputS88.3, InputS88.5, J1.1, J1.2, J4.3, S88.2, U1.2 (GND), U2.8 (VSS), U3.9 (GND2), U3.15 (GND2); also elsewhere on the board
unnamed: C5.1, R4.2, U3.11 (B4)
unnamed: R1.2, U2.2 (Aout)
unnamed: R2.2, U2.4 (Bout)
unnamed: R3.2, U2.6 (Cout)
unnamed: R5.2, U2.9 (Din), U2.11 (Ein), U2.13 (Select), U2.14 (Fin)
unnamed: R6.1, U3.3 (A1)
unnamed: R7.1, U3.4 (A2)
unnamed: R8.1, U3.5 (A3)
unnamed: R9.1, U3.6 (A4)
unnamed: U2.3 (Ain), U3.14 (B1)
unnamed: U2.5 (Bin), U3.13 (B2)
unnamed: U2.7 (Cin), U3.12 (B3)
VDD: C3.1, InputS88.1, J3.2, S88.6, U2.16 (VDD); also elsewhere on the board
